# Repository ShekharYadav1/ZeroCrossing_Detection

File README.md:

This post shows how to implement an isolated zero crossing detection circuit using an analog comparator and optocoupler, circuit schematic is the one below.

Circuit Description:

A zero crossing detector is an electronic circuit used to detect the exact moment when the voltage of an alternating current (AC) signal passes through zero volts. In other words, the zero-crossing detection circuit detects when an AC signal voltage changes from positive to negative and vice versa.

Basically, the zero-crossing detector circuit has an analog input for the AC signal and a logic output that changes with respect to the input AC signal. For example if the input signal is in its positive cycle then the circuit outputs a logic high (or logic low depending on the design of the circuit), and if the input signal is in its negative cycle then the circuit outputs a logic low (or logic high).

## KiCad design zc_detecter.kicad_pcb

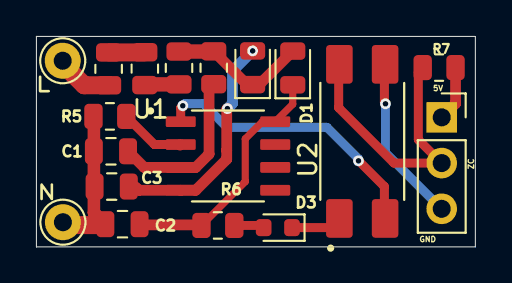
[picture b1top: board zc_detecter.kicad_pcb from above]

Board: 2 copper layers, 24.4 x 11.7 mm, 18 parts (0 on the bottom side), 15 nets.

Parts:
C1, C2, C3: 100nF; C_0805_2012Metric
D1: BAT85; D_0805_2012Metric
D2: BAT84; D_0805_2012Metric
D3: LED; LED_0603_1608Metric
J1: Conn_01x03; PinSocket_1x03_P2.54mm_Vertical
L: AC_L; Pin_D1.0mm_L10.0mm
N: AC_N; Pin_D1.0mm_L10.0mm
R1, R2, R3: 510K; R_0805_2012Metric
R4, R5, R7: 10K; R_0805_2012Metric
R6: 1K; R_0805_2012Metric
U1: LM393; SOIC127P600X175-8N
U2: PC817; SOIC254P960X420-4N

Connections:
+5V: J1.1, R7.2
+5V_ISO: C2.1, D1.1 (K), R6.2, U1.8 (V+)
-5V_ISO: C3.1, D2.2 (A), U1.4 (V-)
GND: J1.3, U2.3
N_GND: C1.2, C2.2, C3.2, N.1, R5.2
unnamed: D1.2 (A), D2.1 (K), R3.2, R4.1
unnamed: D3.2 (A), R6.1
unnamed: D3.1 (K), U2.1
unnamed: J1.2, R7.1, U2.4
unnamed: L.1, R1.1
unnamed: R1.2, R2.1
unnamed: R2.2, R3.1
unnamed: U1.1, U2.2
unnamed: C1.1, R4.2, U1.3 (+)
unnamed: R5.1, U1.2 (-)

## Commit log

2025-11-29 tested
